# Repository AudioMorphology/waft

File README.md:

# waft
Eurorack Gesture Controller

## Overview

Waft is a LIDAR-based gesture controller in Eurorack format.

It is based around the VL6180x Time Of Flight controller, which measures distances using a low-power Infra-red LASER emitter but, unlike most IR distance measuring devices, which estimate distance based on reflected signals, the VL6180x measures the actual round-trip (Time Of Flight) delay. So, maybe 'gesture' perhaps overstates it slightly - it doesn't recognise gestures such as swipe up, swipe down etc., though it _**does**_ measure distance with mm accuracy over a distance of 20cm or thereabouts.... 

The VL6180X is the latest product based on ST Microelectronics'patented FlightSense™ technology. It uses a SPAD (Single Photon Avalanche Diode) array coupled with a VCSEL (Vertical Cavity Surface-Emitting Laser). The VL6180x also incorporates an Ambient Light Sensor, though we're not making use of that here.

Waft utilises the widely-available Arduino Nano V3 board as its processing core, and an mcp4728 12-Bit I2C quad-channel DAC for the CV Outputs.

Waft generates two CV and two Gate outputs:

* CV1 - 0-8v Range, not quantised
* CV2 - 0-2v Range, quantised to a series of selectable scales
* Gate 1 - On if any object detected
* gate 2 - On triggered by movement only

In addition, a CV Input can be mixed with a variable amount of CV1, thus the Waft controller can be used to modulate a CV input.

The hardware design (Schematics & Gerbers) are released under the Open Source Hardware Association (UID UK000005), and the Software is available under a Creative Commons / MIT license.

All documentation is held in the Wiki

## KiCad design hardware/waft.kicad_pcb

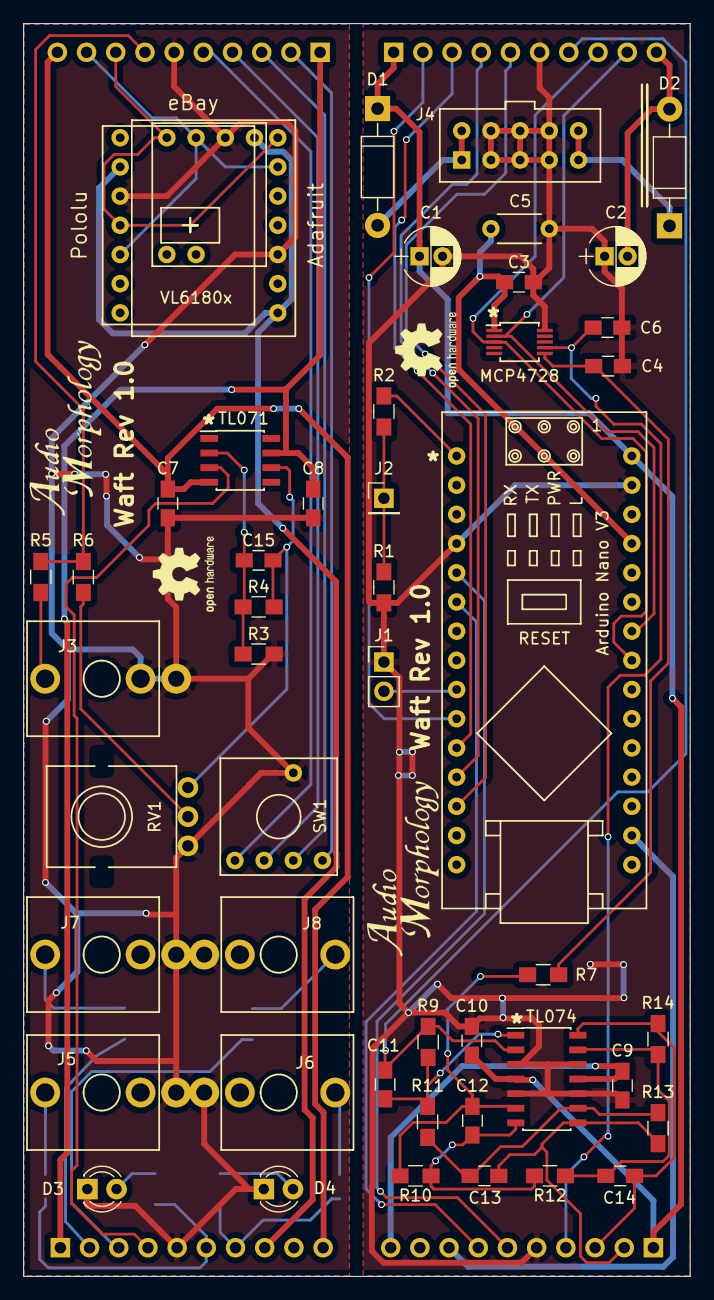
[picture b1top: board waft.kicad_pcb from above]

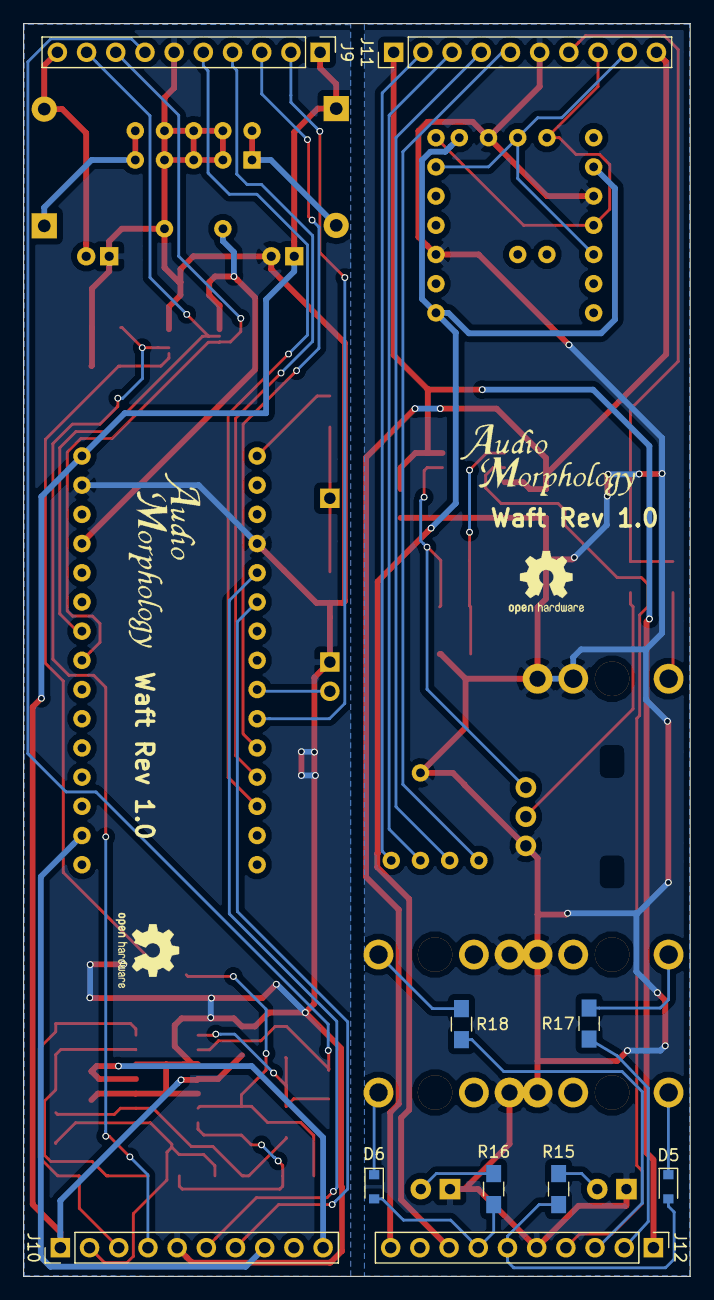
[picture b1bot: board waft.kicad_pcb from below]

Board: 2 copper layers, 58.0 x 109.0 mm, 57 parts (10 on the bottom side), 50 nets.

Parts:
Arduino Nano V3: Arduino_Nano_V3
C1, C2: 10uF; CP_Radial_D5.0mm_P2.00mm
C3: 100n; C_0805_HandSoldering
C4, C6, C7, C8, C9, C10: 10n; C_0805_HandSoldering
C5: 10uF Tant; tantalum_capacitor
C11, C12, C13, C14, C15: 47pF; C_0805_HandSoldering
D1, D2: 1N5817; D_DO-41_SOD81_P10.16mm_Horizontal
D3, D4: LED; LED_D3.0mm
D5, D6: 1N4148; D_0805
J1: CONN_01X02; Pin_Header_Straight_1x02_Pitch2.54mm
J2: CONN_01X01; Pin_Header_Straight_1x01_Pitch2.54mm
J3, J5, J6, J7, J8: Thonkiconn
J4: Conn_02x05_Odd_Even; IDC-2x5
J9, J10: Conn_01x10_Female; Pin_Header_Straight_1x10_Pitch2.54mm
J11, J12: Conn_01x10_Male; Pin_Header_Straight_1x10_Pitch2.54mm
MCP4728: MCP4728; MSOP-10_3x3mm_Pitch0.5mm
R1: 3k3; R_0805_HandSoldering
R2: 2k2; R_0805_HandSoldering
R3, R4, R5, R6, R7, R9, R10, R11, R12, R13, R14: 100k; R_0805_HandSoldering
R15, R16: 1k; R_0805_HandSoldering
R17, R18: 330R; R_0805_HandSoldering
RV1: B100K; Alpha_9mm_Vertical
SW1: Coded_Switch; 10_Way_Coded_Switch
TL071: TL071; SOIC-8_3.9x4.9mm_Pitch1.27mm
TL074: TL074; SOIC-14_3.9x8.7mm_Pitch1.27mm
VL6180x: VL6180x_Composite

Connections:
+3V3: Arduino Nano V3.17, J10.8, J12.8, VL6180x.2, VL6180x.11, VL6180x.14
+5V: Arduino Nano V3.27, C3.1, C5.1, MCP4728.1
+12V: Arduino Nano V3.30, C1.1, C8.2, C10.2, D1.1, J9.1, J10.1, J11.1, J12.1, TL071.7, TL074.4
-12V: C2.2, C7.1, C9.1, D2.2, J9.10, J10.10, J11.10, J12.10, TL071.4, TL074.11
CV1a: C13.1, J10.2, R13.1, TL074.8
CV1b: J12.2, R17.2
CV2a: C14.1, J10.3, R14.1, TL074.14
CV2b: J12.3, R18.2
D0b: J11.2, SW1.2
D1a: Arduino Nano V3.11, J9.3
D1b: J11.3, SW1.3
D2a: Arduino Nano V3.12, J9.4
D2b: J11.4, SW1.4
D3a: Arduino Nano V3.13, J9.5
D3b: J11.5, SW1.5
DAC_A: C4.1, MCP4728.6, R7.2
DAC_Ba: C6.1, J10.4, MCP4728.7
DAC_Bb: J12.4, TL071.3
DIR: Arduino Nano V3.9, J1.2
DOa: Arduino Nano V3.10, J9.2
GATE_1a: Arduino Nano V3.5, J10.6
GATE_1b: D5.2, J12.6, R15.2
GATE_2a: Arduino Nano V3.6, J10.7
GATE_2b: D6.2, J12.7, R16.2
GND: Arduino Nano V3.4, Arduino Nano V3.29, C1.2, C2.1, C3.2, C4.2, C5.2, C6.2, C7.2, C8.1, C9.2, C10.1, D3.1, D4.1, J1.1, J3.1, J3.2, J4.3, J4.4, J4.5, J4.6, J4.7, J4.8, J5.1, J6.1, J7.1, J8.1, J9.6, J10.5, J11.6, J12.5, MCP4728.10, R1.2, R3.2, RV1.3, SW1.1, TL074.3, TL074.5, TL074.10, TL074.12, VL6180x.3, VL6180x.10, VL6180x.16
MIXa: C11.2, J9.7, R9.2, TL074.2
MIXb: J11.7, R5.1, R6.1
unnamed: C11.1, R9.1, R11.2, TL074.1
unnamed: C12.1, R10.1, R12.2, TL074.7
unnamed: C12.2, R7.1, R10.2, TL074.6
unnamed: C13.2, R11.1, R13.2, TL074.9
unnamed: C14.2, R12.1, R14.2, TL074.13
unnamed: C15.1, R4.1, RV1.1, TL071.6
unnamed: C15.2, R3.1, R4.2, TL071.2
unnamed: Arduino Nano V3.1, R2.1
unnamed: D1.2, J4.1, J4.2
unnamed: D2.1, J4.9, J4.10
unnamed: D3.2, R15.1
unnamed: D4.2, R16.1
unnamed: D5.1, J5.3
unnamed: D6.1, J6.3
unnamed: J2.1, R1.1, R2.2
unnamed: J3.3, R5.2
unnamed: J7.3, R17.1
unnamed: J8.3, R18.1
unnamed: R6.2, RV1.2
SCLa: Arduino Nano V3.24, J9.9, MCP4728.2
SCLb: J11.9, VL6180x.5, VL6180x.9, VL6180x.19
SDAa: Arduino Nano V3.23, J9.8, MCP4728.3
SDAb: J11.8, VL6180x.4, VL6180x.8, VL6180x.20

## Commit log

2017-02-12 initial test app
2017-02-26 moved to .CPP source
2017-02-26 new file: waft.ino
2017-03-01 minor update
2017-04-07 Rev 1.0 Schematic upload
2017-04-07 KiCad Library upload
2017-04-11 added support for rotary BCD switch for quantisation selection
2018-01-15 Updated KiCad project-specific footprint & 3D Model
2018-01-15 Schematic changes.
    Couple of changes to the schematic, & started laying out the PCB.
2018-01-16 Started board layout
2018-01-16 Arduino 3D Model
2018-01-16 Top and bottom track routing
2018-01-19 Started Front panel design
2018-01-21 Silk screen graphics
2018-01-21 Added Gerber files for Waft PCB
2018-01-22 final cosmetic adjustments to Rev 1.0 Layout
2018-01-22 Rev 1 Gerbers as sent for fabrication
2018-01-22 Forgot the solder mask layers!
2018-01-22 Initial Bill of Materials
2018-01-29 Rev 1.0 Sent for fabrication
2018-01-29 Rev 1.0 Gerbers as sent for fabrication
2018-01-30 Update KiCad library
2018-02-19 Deleted waft.cpp
2018-02-19 nightly build
2018-02-20 Major scale quantisation
2018-03-03 additional quantisation scales
2021-11-21 Update waft.ino
    Updated Adafruit VL6180X library Name
